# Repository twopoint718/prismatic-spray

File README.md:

# Prismatic Spray 🌈

Designing a handheld RGB widget for light painting.
Named after the D&D spell by the same name.

<figure>
  
  <figcaption>A wizard casting the Prismatic Spray spell</figcaption>
</figure>

## Statechart

This [statechart](https://statecharts.dev/) gives an overview of the operation of Prismatic Spray:

When turned on, the device immediately transitions to the active state.
Conceptually, this initial transition can be seen as when the initialization code runs in the `StateMachine()` constructor.

In the Active state each of the concurrent sub-states for the 4 buttons are initially set
to "Led(N)Off". When a button is pressed down, the corresponding LED will illuminate until the button is released.
Pressing a button also has the side effect of setting the _focused_ LED.
This is the LED for which adjustments of the Hue knob or the Brightness knob will subsequently affect.
Only one LED can be focused like this and it will always be the last button pressed.
If no buttons have been pressed, it is `LED0`. 

The rotary encoder sets the hue/color of the focused LED in 24 equal steps.
These are spaced evenly around the HSL color wheel:

The brightness adjustment uses a potentiometer instead of a rotary encoder like hue.
This means that the brightness is set on an absolute scale from off to 100%.

## Prototype

Short video: https://twitter.com/twopoint718/status/1552858497666240512

## PCB

- [x] split pcb into two files for main and daughter board
- [x] measure height of knobs for case lid clearance

## Resources/Parts Datasheets

- Cherry MX key switch https://gitlab.com/kicad/libraries/kicad-footprints/-/tree/master/Button_Switch_Keyboard.pretty
- Rotary encoder https://cdn-shop.adafruit.com/datasheets/pec11.pdf
  - Knob https://cdn-shop.adafruit.com/datasheets/EPD-200732.pdf
- Potentiometer https://cdn-shop.adafruit.com/datasheets/p160.pdf
  - Knob https://cdn-shop.adafruit.com/product-files/5541/knob+drawing.jpg
- Heat-set insert https://www.mcmaster.com/94180A321/

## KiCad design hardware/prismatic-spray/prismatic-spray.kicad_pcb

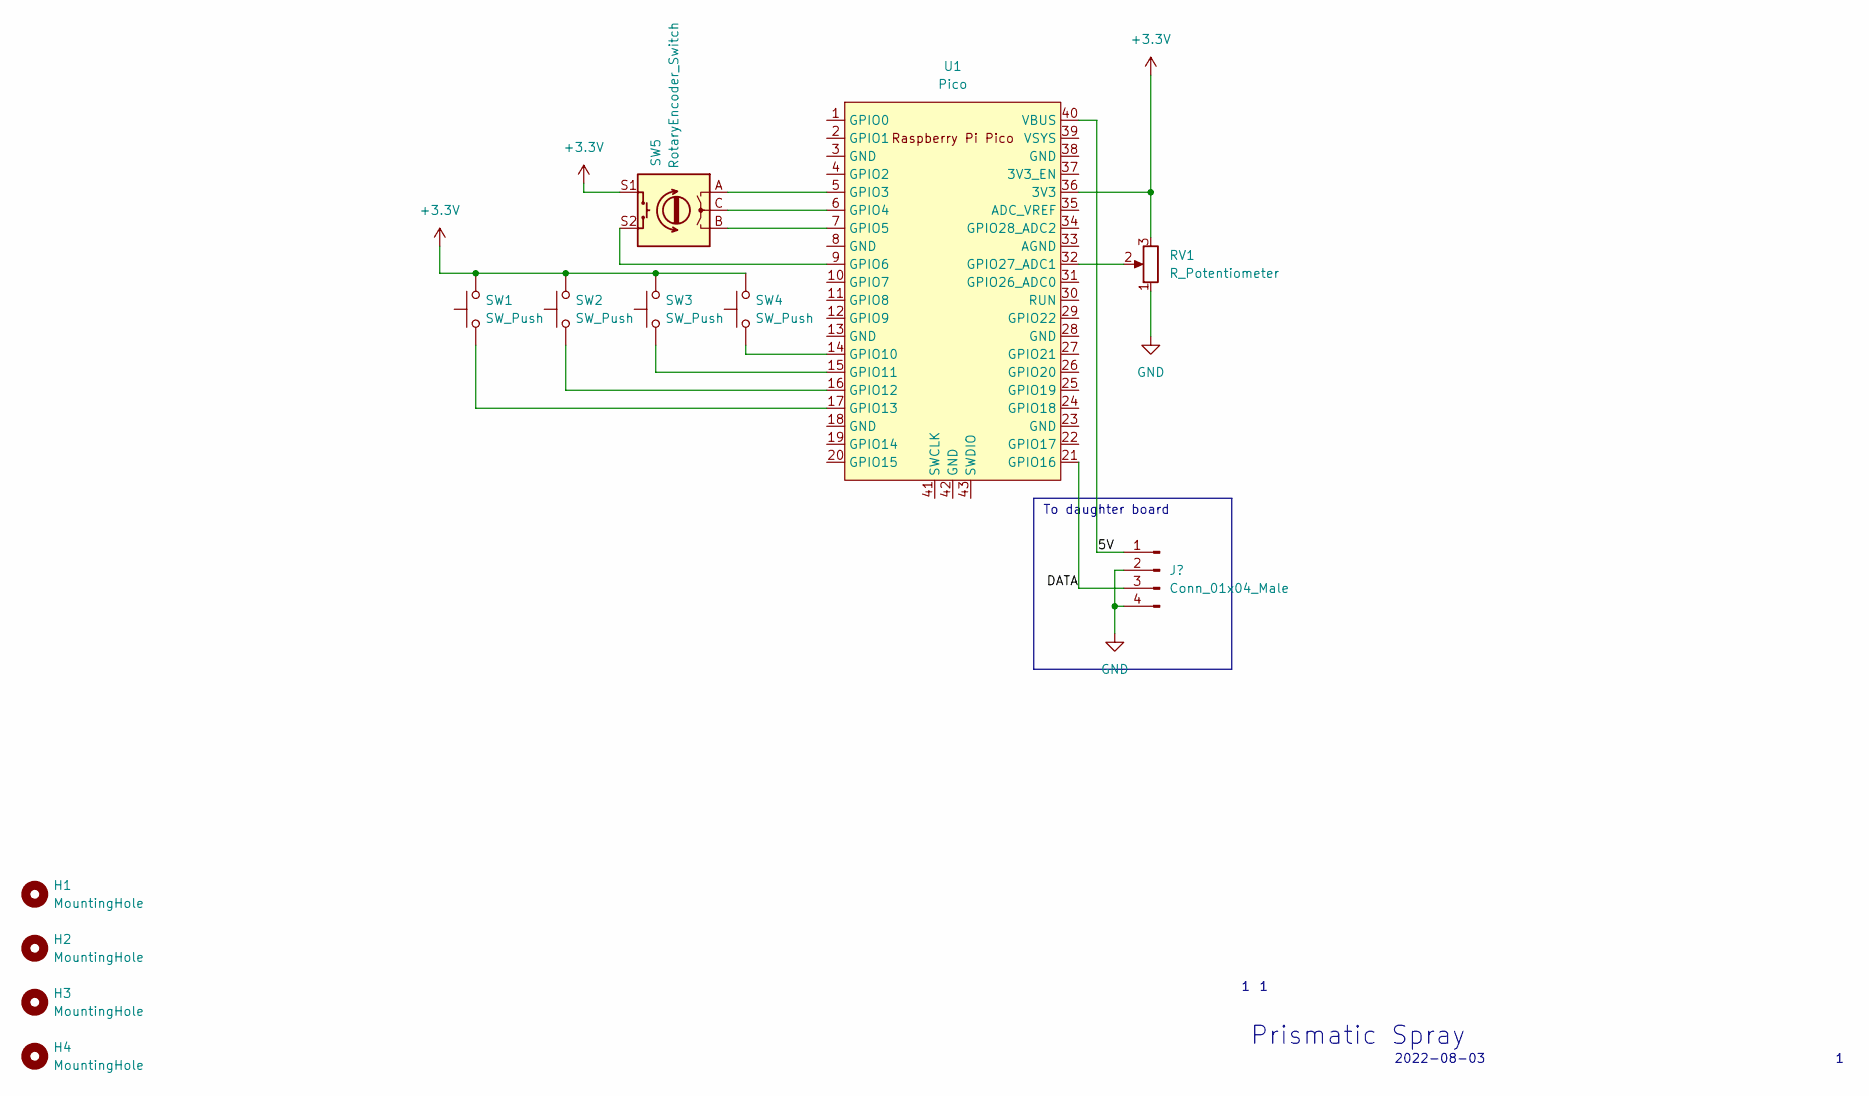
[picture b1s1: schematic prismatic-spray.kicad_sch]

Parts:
H1, H2, H3, H4: MountingHole; MountingHole_2.7mm_M2.5
RV1: R_Potentiometer; p160_potentiometer
SW1, SW2, SW3, SW4: SW_Push; SW_Cherry_MX_1.00u_PCB
SW5: RotaryEncoder_Switch; pec11_rotary_encoder
U1: Pico; RPi_Pico_SMD_TH

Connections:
+3V3: RV1.3, SW1.2, SW2.2, SW3.2, SW4.2, SW5.S1, U1.36 (3V3)
/5V_A: U1.40 (VBUS); also elsewhere on the board
/DATA_A: U1.21 (GPIO16); also elsewhere on the board
GND: RV1.1; also elsewhere on the board
unnamed: RV1.2, U1.32 (GPIO27_ADC1)
unnamed: SW1.1, U1.17 (GPIO13)
unnamed: SW2.1, U1.16 (GPIO12)
unnamed: SW3.1, U1.15 (GPIO11)
unnamed: SW4.1, U1.14 (GPIO10)
unnamed: SW5.A, U1.5 (GPIO3)
unnamed: SW5.C, U1.6 (GPIO4)
unnamed: SW5.B, U1.7 (GPIO5)
unnamed: SW5.S2, U1.9 (GPIO6)

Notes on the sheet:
To daughter board
2022-08-03
Prismatic Spray

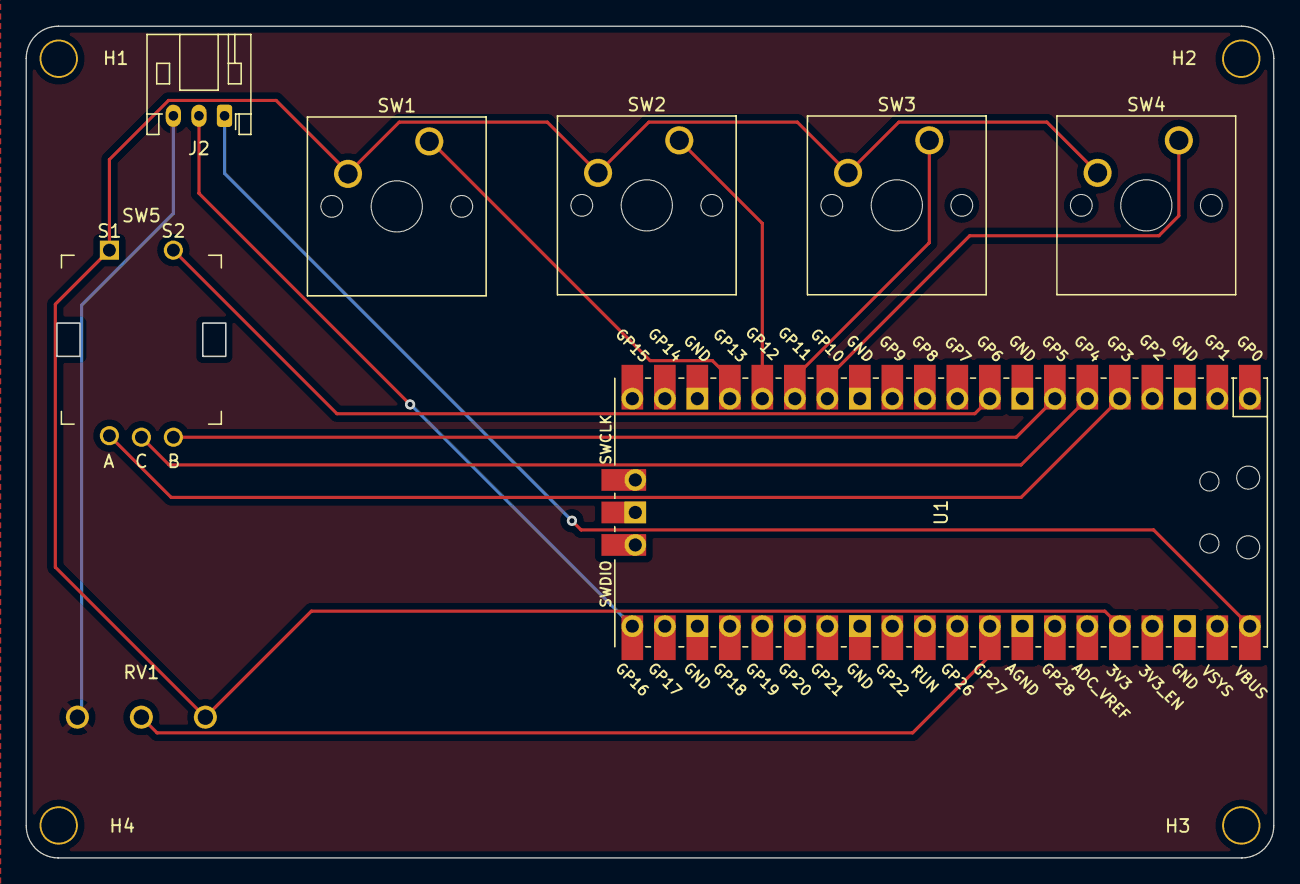
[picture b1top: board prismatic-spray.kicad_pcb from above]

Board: 2 copper layers, 97.5 x 65.0 mm, 12 parts (0 on the bottom side), 13 nets.

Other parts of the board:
J2: Conn_01x03_Male; JST_PH_S3B-PH-K_1x03_P2.00mm_Horizontal

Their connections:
/5V_A: J2.1; also elsewhere on the board
/DATA_A: J2.2; also elsewhere on the board
GND: J2.3; also elsewhere on the board

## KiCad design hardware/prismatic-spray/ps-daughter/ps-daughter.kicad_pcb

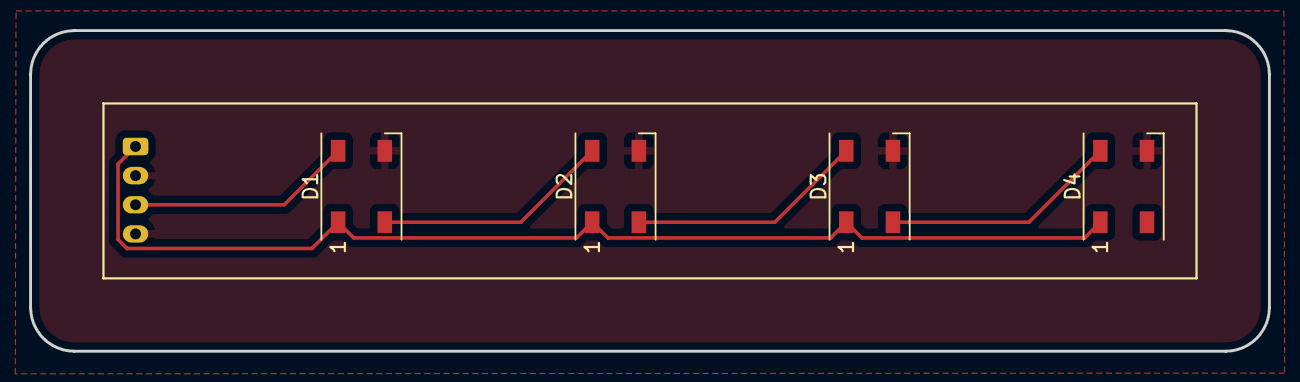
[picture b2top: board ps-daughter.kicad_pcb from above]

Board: 2 copper layers, 85.0 x 22.0 mm, 5 parts (1 on the bottom side), 6 nets.

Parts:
D1, D2, D3, D4: WS2812B; LED_WS2812B_PLCC4_5.0x5.0mm_P3.2mm
J1: Conn_01x04_Male; JST_PH_S4B-PH-K_1x04_P2.00mm_Horizontal

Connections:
+5V: D1.1 (VDD), D2.1 (VDD), D3.1 (VDD), D4.1 (VDD), J1.1
GND: D1.3 (VSS), D2.3 (VSS), D3.3 (VSS), D4.3 (VSS), J1.2, J1.4
unnamed: D1.2 (DOUT), D2.4 (DIN)
unnamed: D1.4 (DIN), J1.3
unnamed: D2.2 (DOUT), D3.4 (DIN)
unnamed: D3.2 (DOUT), D4.4 (DIN)

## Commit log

2022-07-28 Add prototype Circuit Python code
2022-07-28 Rename project
    Update the readme to reference the new project name.
2022-07-29 Add potentiometer to set color (hue)
    - LED turns on when button is pressed
2022-07-29 Add prototype photo and link to video
2022-07-30 Port to MicroPython
2022-08-01 Add 3d file for case design
2022-08-04 Add KiCAD files
2022-08-05 Add 4th button and LED
    Also add a rotary encoder for color control (pot is for brightness)
2022-08-06 Add mounting holes
    - Add non-plated mounting holes
    - Reposition board
    - Place potentiometer
    - TODO: rotary encoder
2022-08-07 Populate board with more footprints/3d models
    - Add Cherry MX key switch 3d model
    - Add PEC11 rotary encoder 3d model
    - Add Raspberry Pi Pico 3d model
    - Add PEC11 footprint (from schematic)
    - Change rotary encoder schematic symbol to 3 encoder pins + 2 switch pins
    - Add PCB rendering for docs
2022-08-09 Add P160 Potentiometer
    - Add custom footprint
    - TODO: add outline/screenprint for PCB size
2022-08-10 Route most traces
    - Route most traces on main board and daughter board
    - Add mounting holes to daughter board
    - Flip daughterboard connector to back of PCB
    - Reassign some GPIOs for better routing
    - Fix footprint for pec11 to get clean DRC
2022-08-10 Add dimentions to PCB
2022-08-11 Add first draft state machine
2022-08-12 Refactor to a state machine
    - Add state machine graphviz file
2022-08-16 Separate boards into different schematics
    KiCAD: 1 board = 1 project
    So sayeth the forums:
    https://forum.kicad.info/t/hooking-up-a-separate-board-to-the-main-one-with-a-cable/37093
2022-08-30 PCB Rev 1
    Hardware rev 1
    - Main board
    - Daughter board
2022-09-04 Move code into `firmware`
2022-09-04 Create state diagram
2022-09-04 WIP: state machine
2022-09-05 Starting tests on state machine
2022-09-07 Use concurrent states ↔️
2022-09-09 Update README
    - Add code to generate a png showing the color palette
    - Update state machine diagram
2022-09-09 Add test for increment wraparound
2022-09-27 Add rendered image
2022-09-28 Update case (WIP)
    Case WIP
    - modeling the main board and daughter board for fit
    - bottom portion of the case is good, working on the top and connecting the two
2022-09-29 Knobs
2022-10-14 Add LICENSE
2022-10-21 WIP: Update case design
    WIP: Redesign case using the ideas of this video for a
    snap-together lid: https://youtu.be/VVmOtM60VWw
2022-10-23 Punch holes in the case lid for buttons & knob
2022-10-24 finished case
2022-10-25 v1 of case
    I think the STL file is essentially complete.
2022-10-28 Revise CAD based on measurements
    After printing the first version, took some measurements and moved the side charging USB port
2022-11-28 Add tests for BSP

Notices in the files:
README.md:
License: CERN-OHL-P
